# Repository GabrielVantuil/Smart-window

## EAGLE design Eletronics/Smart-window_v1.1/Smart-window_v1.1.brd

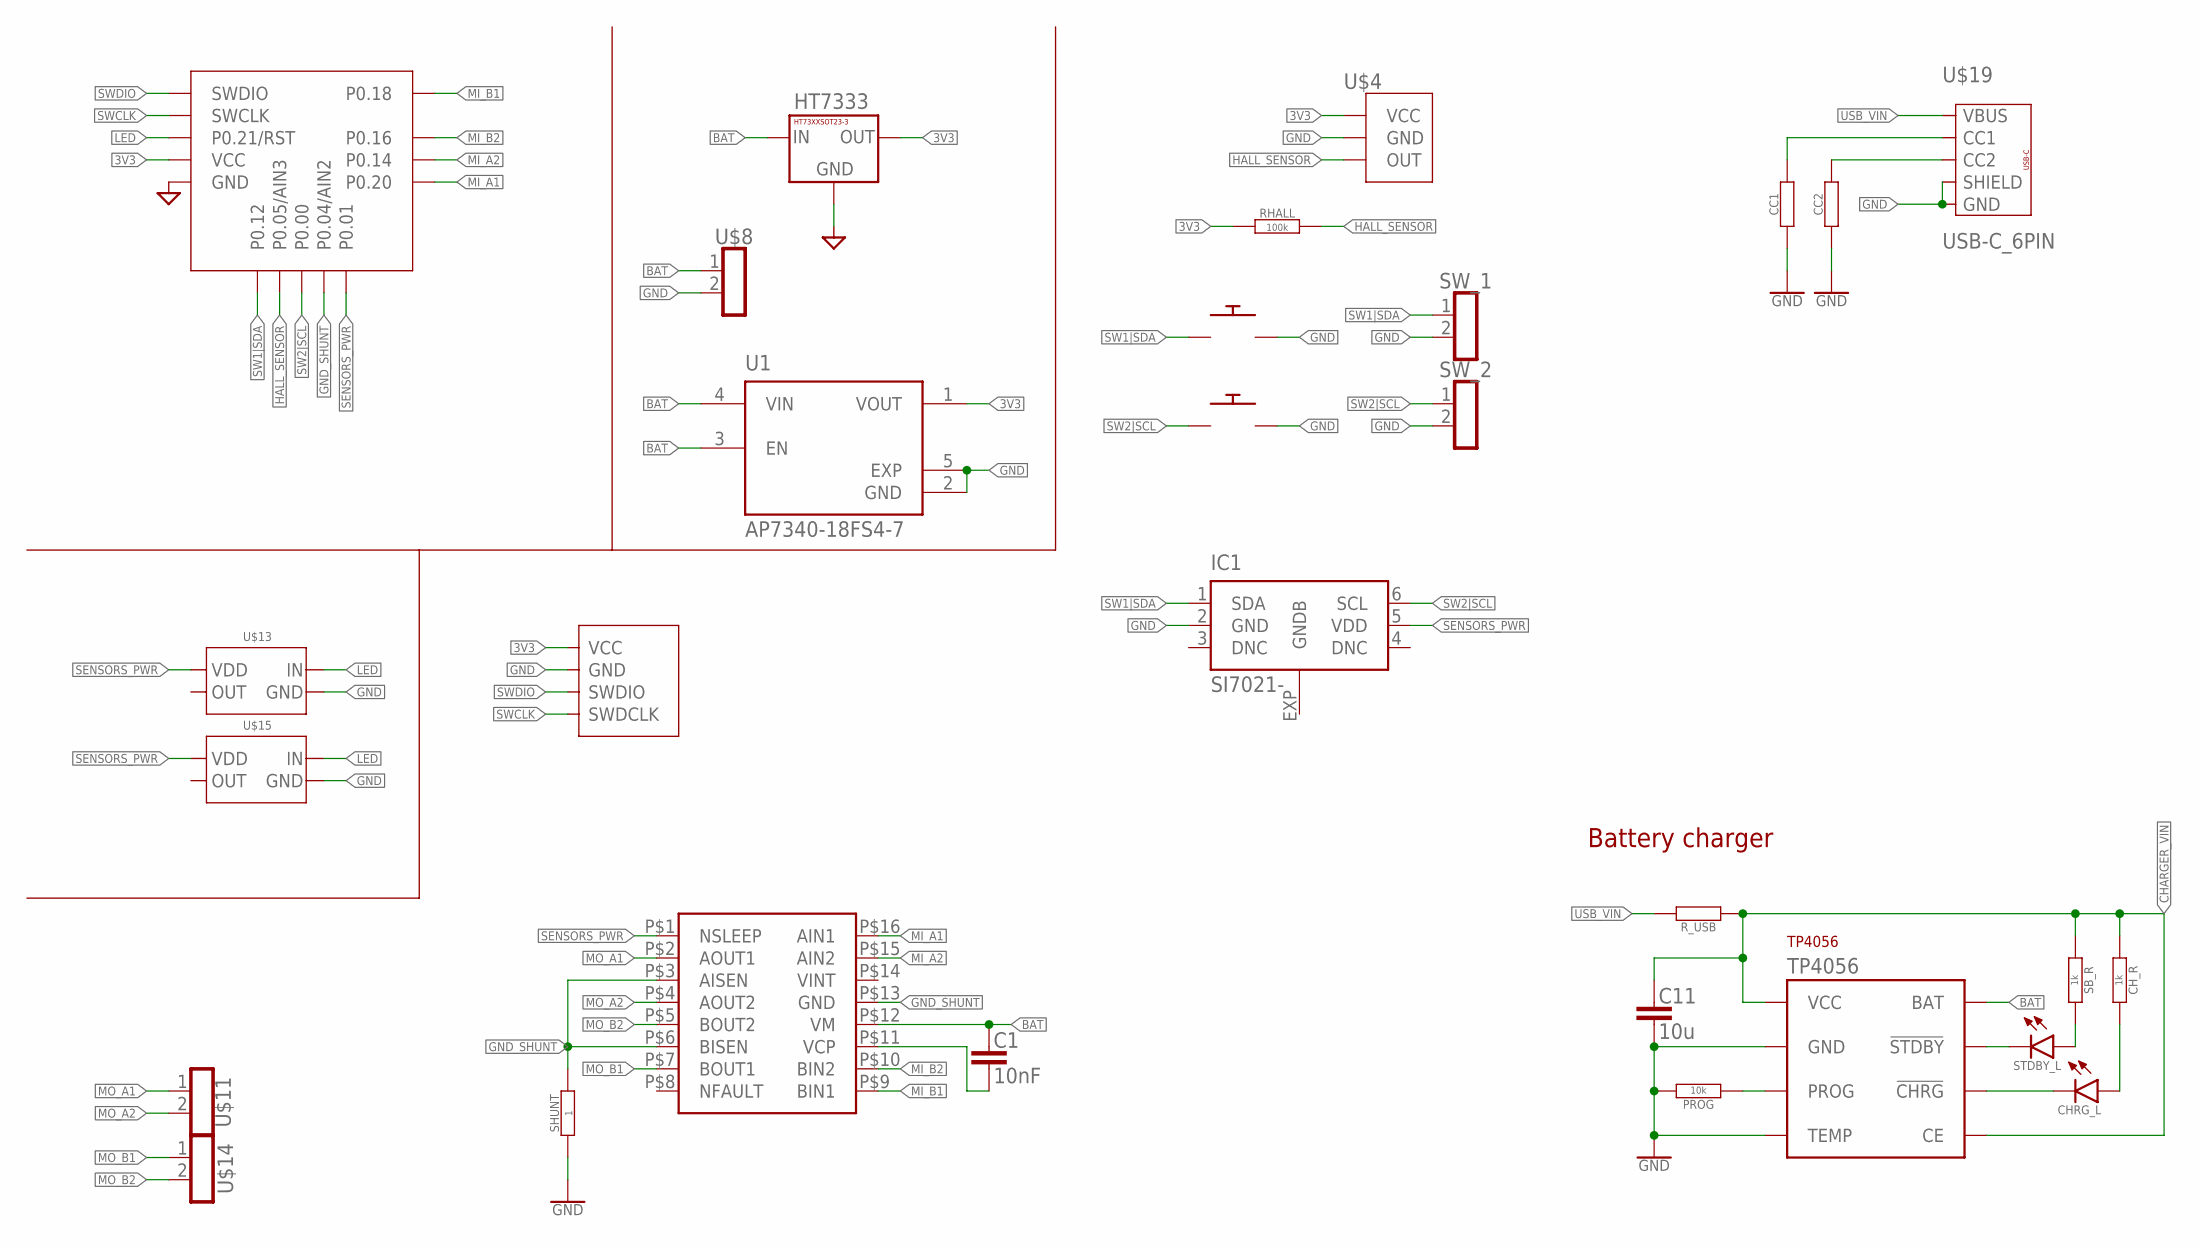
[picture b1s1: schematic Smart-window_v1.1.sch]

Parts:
C1: 10nF; 0402-CAP
C11: 10u; 0402-CAP
CC1, CC2: RESISTOR0402-RES; 0402-RES
CHRG_L: LED_0402; 0402
CH_R: 1k; 0402-RES
HT7333: HT73XXSOT23-3; SOT23-3
IC1: SI7021-; DFN6-3X3
PROG: 10k; 0402-RES
RHALL: 100k; 0402-RES
R_USB: RESISTOR0402-RES; 0402-RES
SB_R: 1k; 0402-RES
SHUNT: 1; 0402-RES
STDBY_L: LED_0402; 0402
SW1, SW2: PUSHBUTTON_3X3_SMALL_FOOTPRINT; PUSHBUTTON_3X3MM_(SMALL_FOOTPRINT)
SW_1, SW_2: PINH1X02_2MM; 1X02_2MM
TP4056: TP4056_SOP8; SOP8
U1: AP7340-18FS4-7; VREG_AP7340-18FS4-7
U$2: E104-BT5005A
U$4: 49E; TO92_HALLSENSOR
U$8, U$11, U$14: PINH1X02_2MM; 1X02_2MM
U$9: GV_SWD_4P_SEMI_SMD_SMALL_BACK; GV_SWD_1.27MM_4P_SEMI_SMD_SMALL_BACK
U$12: DRV8833_; SSOP16
U$13, U$15: SK6805; LED_ARGB
U$19: USB-C_6PIN; USCX-06FX-XXMX-01

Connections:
3V3: HT7333.2 (3.OUT), RHALL.1, U1.1 (VOUT), U$2.VCC, U$4.VCC, U$9.VCC, U$9.VCC1 (VCC)
BAT: C1.1, HT7333.3 (1.IN), TP4056.P$5 (BAT), U1.3 (EN), U1.4 (VIN), U$8.1, U$12.P$12 (VM)
CHARGER_VIN: C11.1, CH_R.1, R_USB.1, SB_R.1, TP4056.P$4 (VCC), TP4056.P$8 (CE)
GND: C11.2, CC1.1, CC2.1, HT7333.1 (2.GND), IC1.2 (GND), PROG.2, SHUNT.1, SW1.1, SW1.2, SW2.1, SW2.2, SW_1.2, SW_2.2, TP4056.P$1 (TEMP), TP4056.P$3 (GND), U1.2 (GND), U1.5 (EXP), U$2.GND, U$2.GND1 (GND), U$4.GND, U$8.2, U$9.GND, U$9.GND1 (GND), U$13.4 (GND), U$15.4 (GND), U$19.GND1 (GND), U$19.GND2 (GND), U$19.SHIELD1 (SHIELD), U$19.SHIELD2 (SHIELD), U$19.SHIELD3 (SHIELD), U$19.SHIELD4 (SHIELD)
GND_SHUNT: SHUNT.2, U$2.P0.04 (P0.04/AIN2), U$12.P$3 (AISEN), U$12.P$6 (BISEN), U$12.P$13 (GND)
HALL_SENSOR: RHALL.2, U$2.P0.05 (P0.05/AIN3), U$4.OUT
LED: U$2.P0.21/RST, U$13.1 (IN), U$15.1 (IN)
MI_A1: U$2.P0.20, U$12.P$16 (AIN1)
MI_A2: U$2.P0.14, U$12.P$15 (AIN2)
MI_B1: U$2.P0.18, U$12.P$9 (BIN1)
MI_B2: U$2.P0.16, U$12.P$10 (BIN2)
MO_A1: U$11.1, U$12.P$2 (AOUT1)
MO_A2: U$11.2, U$12.P$4 (AOUT2)
MO_B1: U$12.P$7 (BOUT1), U$14.1
MO_B2: U$12.P$5 (BOUT2), U$14.2
unnamed: CHRG_L.C, TP4056.P$7 (!CHRG)
unnamed: C1.2, U$12.P$11 (VCP)
unnamed: CC2.2, U$19.CC2
unnamed: STDBY_L.C, TP4056.P$6 (!STDBY)
unnamed: CC1.2, U$19.CC1
unnamed: PROG.1, TP4056.P$2 (PROG)
unnamed: SB_R.2, STDBY_L.A
unnamed: CHRG_L.A, CH_R.2
SENSORS_PWR: IC1.5 (VDD), U$2.P0.01, U$12.P$1 (NSLEEP), U$13.2 (VDD), U$15.2 (VDD)
SW1|SDA: IC1.1 (SDA), SW1.3, SW1.4, SW_1.1, U$2.P0.12
SW2|SCL: IC1.6 (SCL), SW2.3, SW2.4, SW_2.1, U$2.P0.00
SWCLK: U$2.SWCLK, U$9.SWDCLK
SWDIO: U$2.SWDIO, U$9.SWDIO
USB_VIN: R_USB.2, U$19.VBUS1 (VBUS), U$19.VBUS2 (VBUS)

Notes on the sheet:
Battery charger

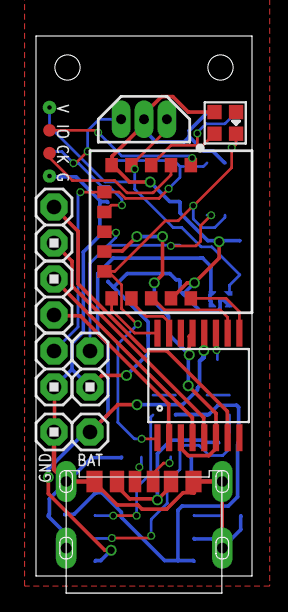
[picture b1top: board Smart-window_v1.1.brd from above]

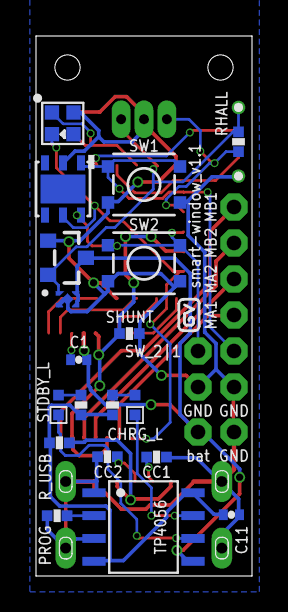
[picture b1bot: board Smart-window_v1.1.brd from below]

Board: 2 copper layers, 12.0 x 30.0 mm, 33 parts (20 on the bottom side), 29 nets.

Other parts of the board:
U$3, U$5: M1.4_SCREW
U$10: GV_2MM

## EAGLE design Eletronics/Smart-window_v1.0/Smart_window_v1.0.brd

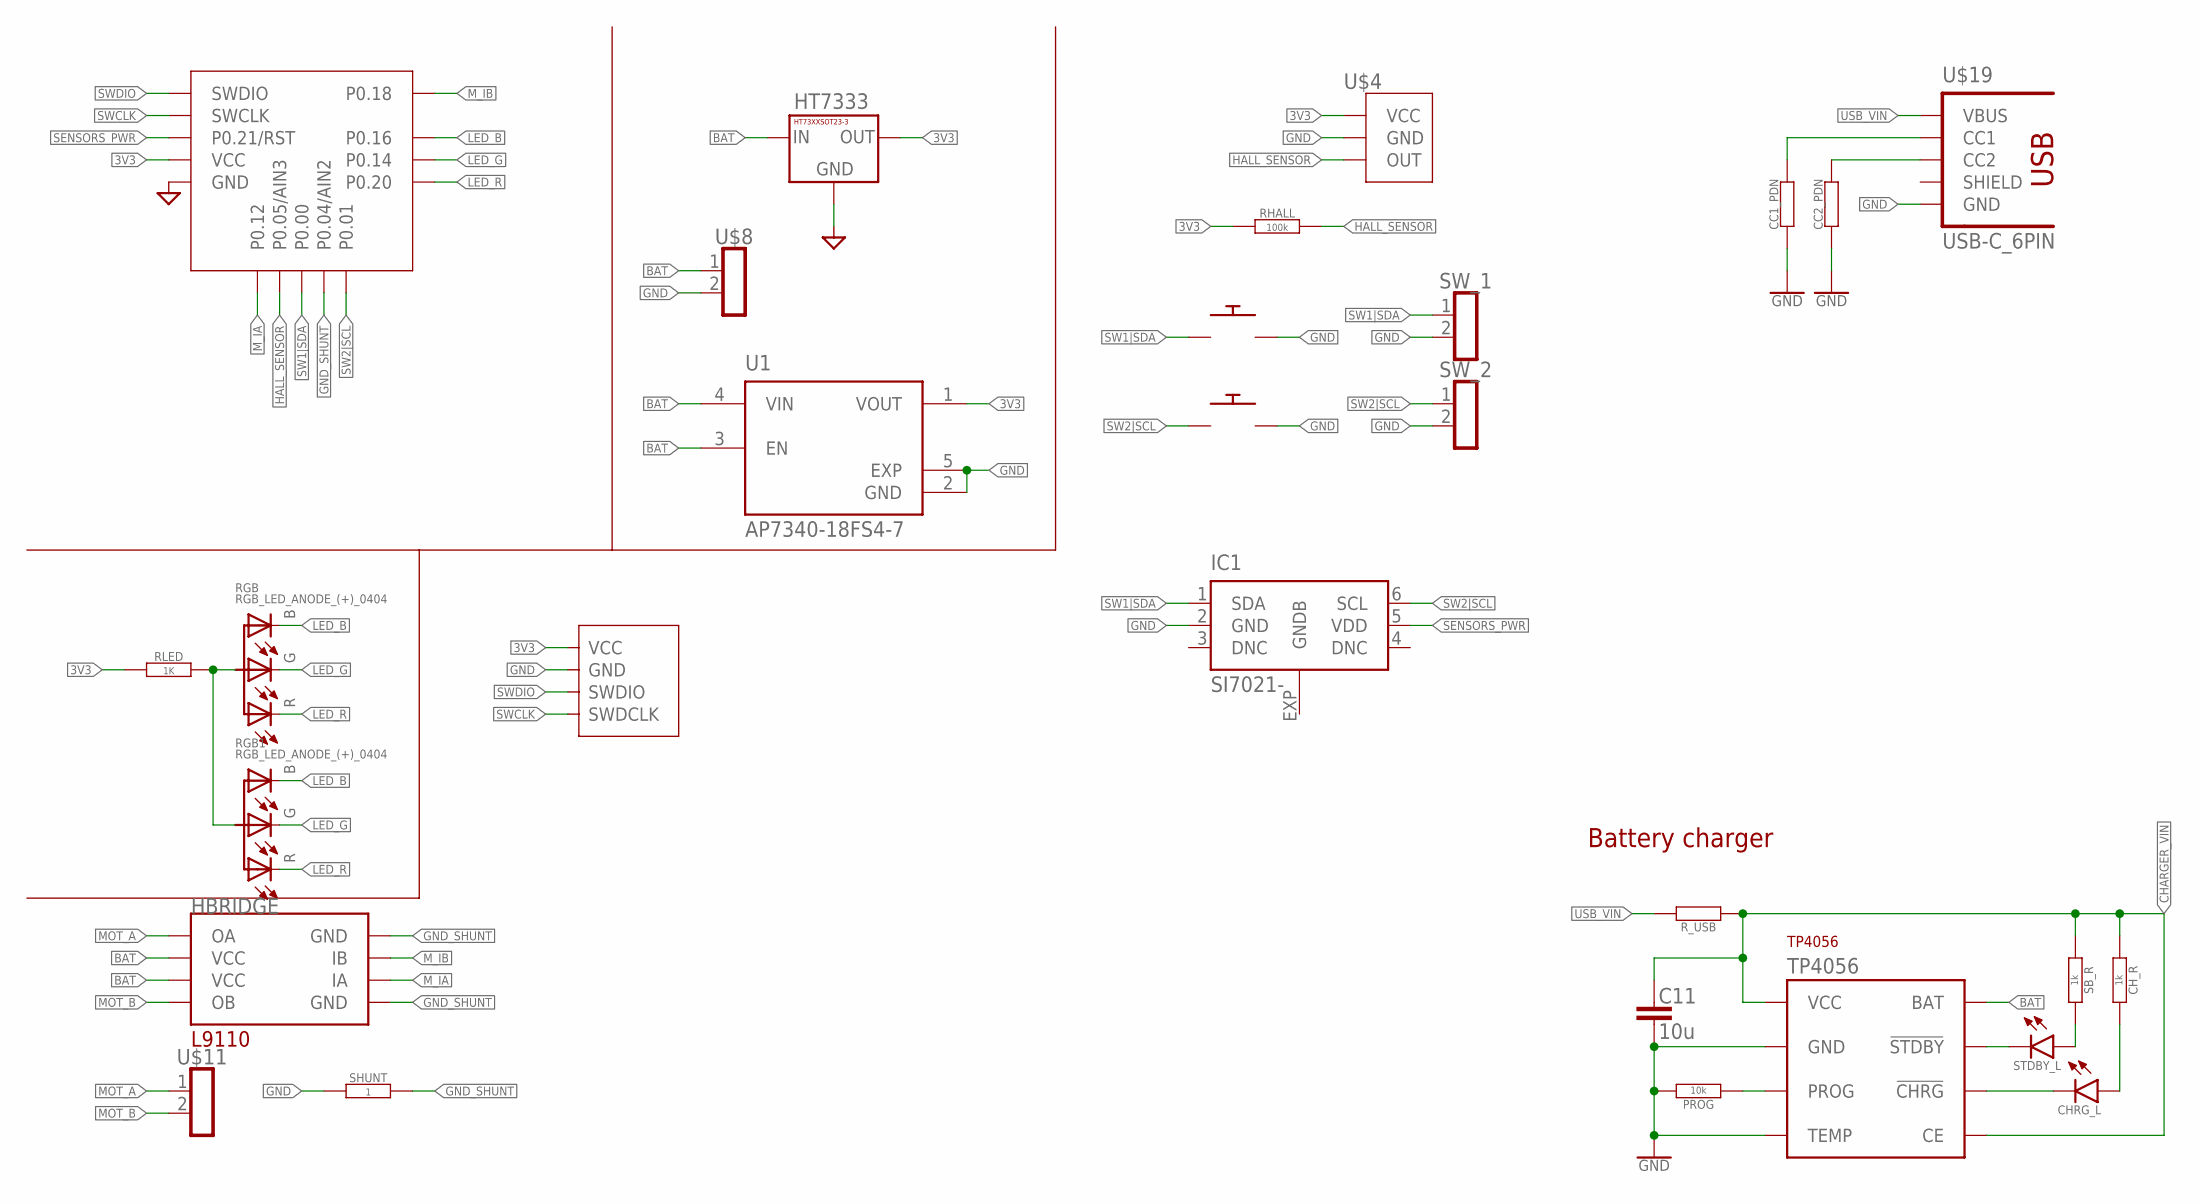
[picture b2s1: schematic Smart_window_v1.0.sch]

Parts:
C11: 10u; 0402-CAP
CC1_PDN, CC2_PDN: RESISTOR0402-RES; 0402-RES
CHRG_L: LED_0402; 0402
CH_R: 1k; 0402-RES
HBRIDGE: L9110; SOP8
HT7333: HT73XXSOT23-3; SOT23-3
IC1: SI7021-; DFN6-3X3
PROG: 10k; 0402-RES
RGB, RGB1: RGB_LED_ANODE_(+)_0404; 0404
RHALL: 100k; 0402-RES
RLED: 1K; 0402-RES
R_USB: RESISTOR0402-RES; 0402-RES
SB_R: 1k; 0402-RES
SHUNT: 1; 0402-RES
STDBY_L: LED_0402; 0402
SW1, SW2: PUSHBUTTON_3X3_SMALL_FOOTPRINT; PUSHBUTTON_3X3MM_(SMALL_FOOTPRINT)
SW_1, SW_2: PINH1X02_2MM; 1X02_2MM
TP4056: TP4056_SOP8; SOP8
U1: AP7340-18FS4-7; VREG_AP7340-18FS4-7
U$2: E104-BT5005A
U$4: 49E; TO92_HALLSENSOR
U$8: PINH1X02; 1X02
U$9: GV_SWD_4P; GV_SWD_1.27MM_4P_SEMI_SMD
U$11: PINH1X02_2MM; 1X02_2MM
U$19: USB-C_6PIN; USCX-06FX-XXMX-01

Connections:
3V3: HT7333.2 (3.OUT), RHALL.1, RLED.1, U1.1 (VOUT), U$2.VCC, U$4.VCC, U$9.VCC
BAT: HBRIDGE.P$2 (VCC), HBRIDGE.P$3 (VCC), HT7333.3 (1.IN), TP4056.P$5 (BAT), U1.3 (EN), U1.4 (VIN), U$8.1
CHARGER_VIN: C11.1, CH_R.1, R_USB.1, SB_R.1, TP4056.P$4 (VCC), TP4056.P$8 (CE)
GND: C11.2, CC1_PDN.1, CC2_PDN.1, HT7333.1 (2.GND), IC1.2 (GND), PROG.2, SHUNT.1, SW1.1, SW1.2, SW2.1, SW2.2, SW_1.2, SW_2.2, TP4056.P$1 (TEMP), TP4056.P$3 (GND), U1.2 (GND), U1.5 (EXP), U$2.GND, U$2.GND1 (GND), U$4.GND, U$8.2, U$9.GND, U$19.GND1 (GND), U$19.GND2 (GND)
GND_SHUNT: HBRIDGE.P$5 (GND), HBRIDGE.P$8 (GND), SHUNT.2, U$2.P0.04 (P0.04/AIN2)
HALL_SENSOR: RHALL.2, U$2.P0.05 (P0.05/AIN3), U$4.OUT
LED_B: RGB.B (LED_BLUE), RGB1.B (LED_BLUE), U$2.P0.16
LED_G: RGB.G (LED_GREEN), RGB1.G (LED_GREEN), U$2.P0.14
LED_R: RGB.R (LED_RED), RGB1.R (LED_RED), U$2.P0.20
MOT_A: HBRIDGE.P$1 (OA), U$11.1
MOT_B: HBRIDGE.P$4 (OB), U$11.2
M_IA: HBRIDGE.P$6 (IA), U$2.P0.12
M_IB: HBRIDGE.P$7 (IB), U$2.P0.18
unnamed: RGB.COM (COMMON_ANODE), RGB1.COM (COMMON_ANODE), RLED.2
unnamed: CHRG_L.C, TP4056.P$7 (!CHRG)
unnamed: CC2_PDN.2, U$19.CC2
unnamed: STDBY_L.C, TP4056.P$6 (!STDBY)
unnamed: CC1_PDN.2, U$19.CC1
unnamed: PROG.1, TP4056.P$2 (PROG)
unnamed: SB_R.2, STDBY_L.A
unnamed: CHRG_L.A, CH_R.2
SENSORS_PWR: IC1.5 (VDD), U$2.P0.21/RST
SHIELD: U$19.SHIELD1 (SHIELD), U$19.SHIELD2 (SHIELD), U$19.SHIELD3 (SHIELD), U$19.SHIELD4 (SHIELD)
SW1|SDA: IC1.1 (SDA), SW1.3, SW1.4, SW_1.1, U$2.P0.00
SW2|SCL: IC1.6 (SCL), SW2.3, SW2.4, SW_2.1, U$2.P0.01
SWCLK: U$2.SWCLK, U$9.SWDCLK
SWDIO: U$2.SWDIO, U$9.SWDIO
USB_VIN: R_USB.2, U$19.VBUS1 (VBUS), U$19.VBUS2 (VBUS)

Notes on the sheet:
Battery charger

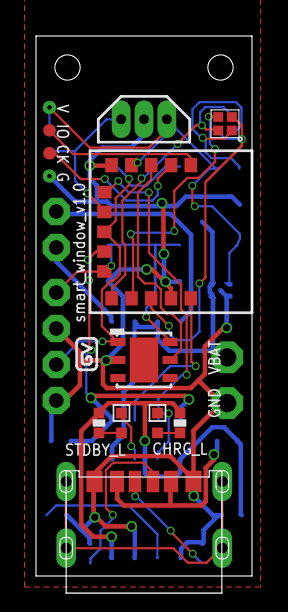
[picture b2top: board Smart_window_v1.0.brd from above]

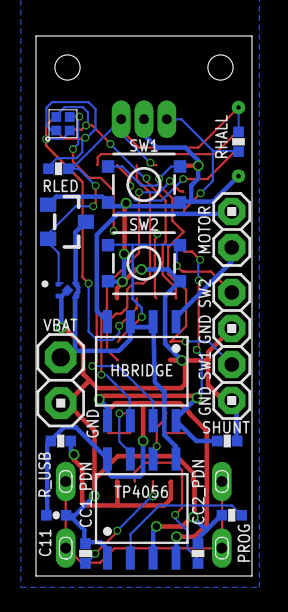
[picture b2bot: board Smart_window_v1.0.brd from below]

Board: 2 copper layers, 12.0 x 30.0 mm, 32 parts (19 on the bottom side), 28 nets.

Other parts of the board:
U$3, U$5: M1.4_SCREW
U$10: GV_2MM

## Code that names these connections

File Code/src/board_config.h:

#ifndef BOARD_CONFIG_H
#define BOARD_CONFIG_H

#define LED_ON	1
#define LED_OFF	0

#define SENSORS_PWR_PIN	01
#define HALL_SENSOR_PIN	05
#define SW1_PIN	   		12
#define SW2_PIN	   		00

#define MI_A1_PIN	   	20
#define MI_A2_PIN	   	14
#define MI_B2_PIN	   	16
#define MI_B1_PIN	   	18

#define SHUNT_PIN	   	04

#define LED_PIN	   		21

#endif

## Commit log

2025-02-08 Smart_window_v1.0
2025-10-26 Code - (testing version)
2025-10-26 Smart-window_v1.1
2025-10-27 Motor code, BLE working
2025-10-30 Adding scheduling and change of protocol: only one command at a time, 2^32ms
2025-10-30 CAD: Lid
